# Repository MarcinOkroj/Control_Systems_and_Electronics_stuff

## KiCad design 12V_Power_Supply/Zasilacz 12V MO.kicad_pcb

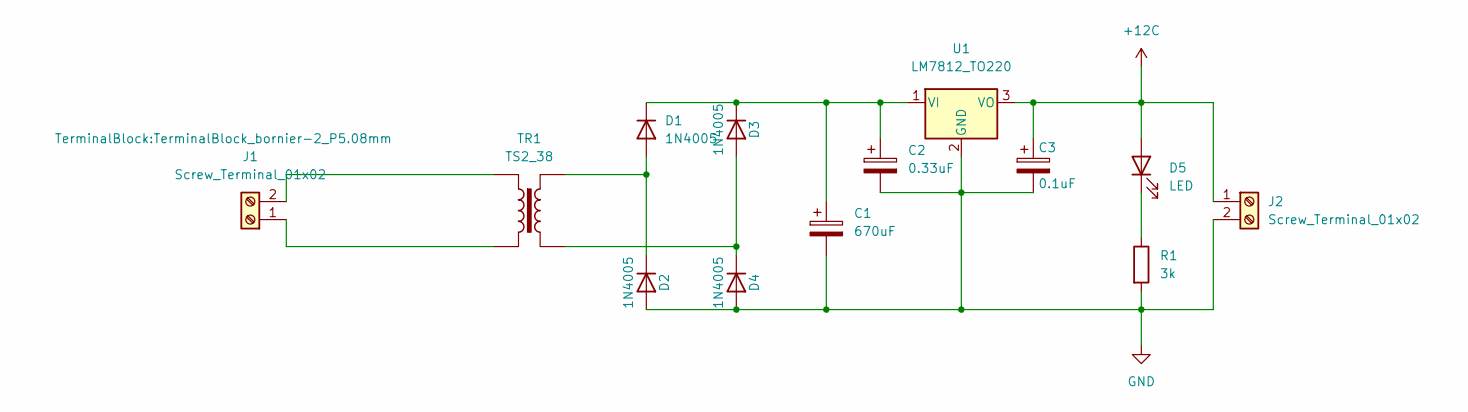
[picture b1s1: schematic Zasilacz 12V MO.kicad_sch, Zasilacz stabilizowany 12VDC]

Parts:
C1: 670uF; CP_Radial_D8.0mm_P3.50mm
C2: 0.33uF; C_Disc_D3.8mm_W2.6mm_P2.50mm
C3: 0.1uF; C_Disc_D3.8mm_W2.6mm_P2.50mm
D1, D2, D3, D4: 1N4005; D_DO-41_SOD81_P10.16mm_Horizontal
D5: LED; LED_D3.0mm
J1, J2: Screw_Terminal_01x02; TerminalBlock_bornier-2_P5.08mm
R1: 3k; R_Axial_DIN0309_L9.0mm_D3.2mm_P12.70mm_Horizontal
TR1: TS2_38; Transformer_37x44
U1: LM7812_TO220; TO-220-3_Vertical

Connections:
+12C: C3.1, D5.2 (A), J2.1, U1.3 (VO)
GND: C1.2, C2.2, C3.2, D2.2 (A), D4.2 (A), J2.2, R1.2, U1.2 (GND)
unnamed: C1.1, C2.1, D1.1 (K), D3.1 (K), U1.1 (VI)
unnamed: D1.2 (A), D2.1 (K), TR1.4
unnamed: D3.2 (A), D4.1 (K), TR1.3
unnamed: D5.1 (K), R1.1
unnamed: J1.1, TR1.2
unnamed: J1.2, TR1.1

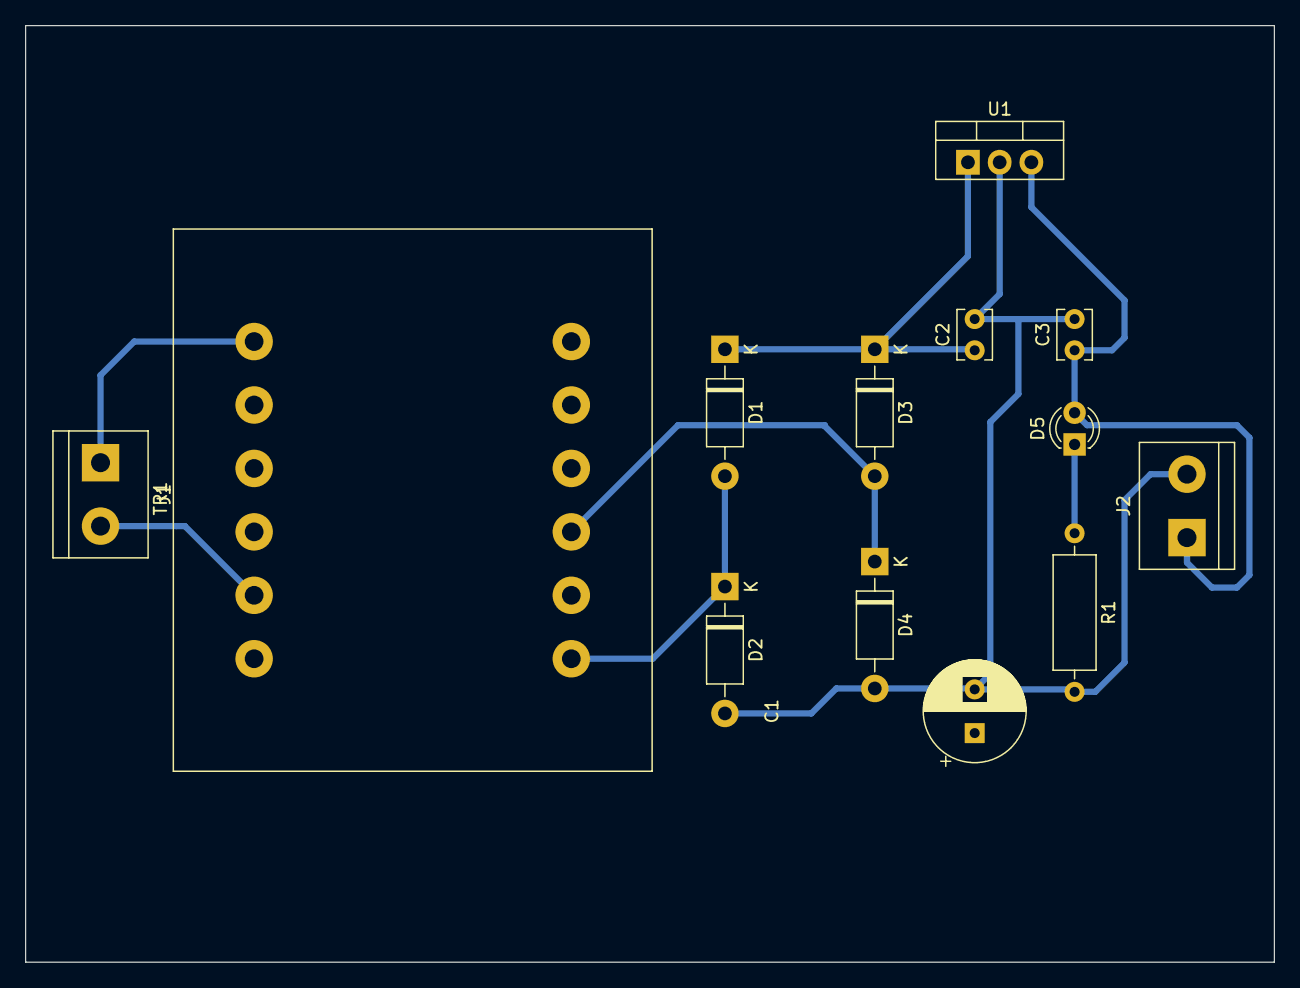
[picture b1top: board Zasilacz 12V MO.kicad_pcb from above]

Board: 2 copper layers, 100.0 x 75.0 mm, 13 parts (0 on the bottom side), 8 nets.

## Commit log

2023-04-12 Inital Commit
2023-04-12 PUZIS added
